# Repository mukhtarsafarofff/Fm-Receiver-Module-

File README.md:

(ENG)  Assembling an FM radio was always interesting for me , like another enthusiasts.  Outside of the TDA7000 IC there is only one tunable LC circuit for the local oscillator . So complete FM radio can be made enough small to be fit inside cigarette lighter.The audio output of the receiver is amplified through LM386 amplifier chip that can drive a small speaker or headphones. Thehe superheterodine receiver: the mixer, the oscillator, the IF amplifier, the amplitude limiter, the FM detector and few others.The station signal is from the (telescopiut circuit that consists of L2, C13, C12 and C14. It is a parallel oscillatory circuit damped with R3 resistor, which has the reception bandwidth from 88 MHz till 108 MHz (it admits all the UHF signals on the pin 13, and weakens te signals outside the reception bandwidth). Inside the IC the s
(DEU) Das Zusammenbauen eines UKW-Radios war für mich immer interessant, wie auch für andere Enthusiasten. Außerhalb des TDA7000 IC gibt es nur einen einstellbaren LC-Schwingkreis für den lokalen Oszillator. So kann ein komplettes UKW-Radio klein genug gebaut werden, um in ein Feuerzeug zu passen. Der Audioausgang des Empfängers wird durch den LM386 Verstärkerchip verstärkt, der einen kleinen Lautsprecher oder Kopfhörer antreiben kann. Das elektronische Diagramm des HF-Teils des Geräts (von der Antenne bis zum NF-Ausgang) mit dem TDA7000 ist auf Bild 4.7 dargestellt. Wie man sehen kann, ist es ein einfaches Gerät, das mit einer relativ kleinen Anzahl von Komponenten gebaut ist. Der IC enthält alle Stufen des Überlagerungsempfängers: den Mischer, den Oszillator, den ZF-Verstärker, den Amplitudenbegrenzer, den FM-Detektor und einige andere. Das Signals der Station wird von der (teleskopischen) Antenne zum Eingangskreis geführt, der aus L2, C13, C12 und C14 besteht. Es ist ein gedämpfter Parallelschwingkreis mit einem R3-Widerstand, der eine Empfangsbandbreite von 88 MHz bis 108 MHz hat (er lässt alle UHF-Signale am Pin 13 zu und schwächt die Signale außerhalb der Empfangsbandbreite ab). Innerhalb des IC werden die Signale in den Mischer geleitet, wo sie neue Trägerfrequenzen erhalten.  Der ZF-Verstärker folgt dann, der nur eines dieser Signale verstärkt, dessen Frequenz gleich der Zwischenfrequenz ist, gefolgt vom Begrenzer, dem FM-Detektor, dem Stummschaltkreis und dem NF-Vorverstärker.  Der Schwingkreis des lokalen Oszillators (L1, Cp, Cs, C und C5) ist zwischen den Pins 5 und 6 geschaltet.  Bild 4.8-a zeigt die Leiterplatte des Geräts von Bild 4.7, während Bild 4.8-b das Komponentenlayout (auf der Leiterplatte) enthält.  Das komplette Gerät ist auf Bild 4.8-c zu sehen.  Der variable Kondensator von Bild 3.8 wird hier als einziger variabler Kondensator verwendet, da der Eingangskreis aperiodisch ist, die Beine mit FO und G gekennzeichnet sind.  Dieser Kondensator dient dazu, den Empfänger auf Stationen einzustellen.  Im NF-Teil des Empfängers wird der Verstärker, der mit dem LM386 von Bild 3.19 gebaut ist, verwendet (die Teile links vom Potentiometer sind weggelassen). L1 und L2 sind die selbsttragenden Spulen.

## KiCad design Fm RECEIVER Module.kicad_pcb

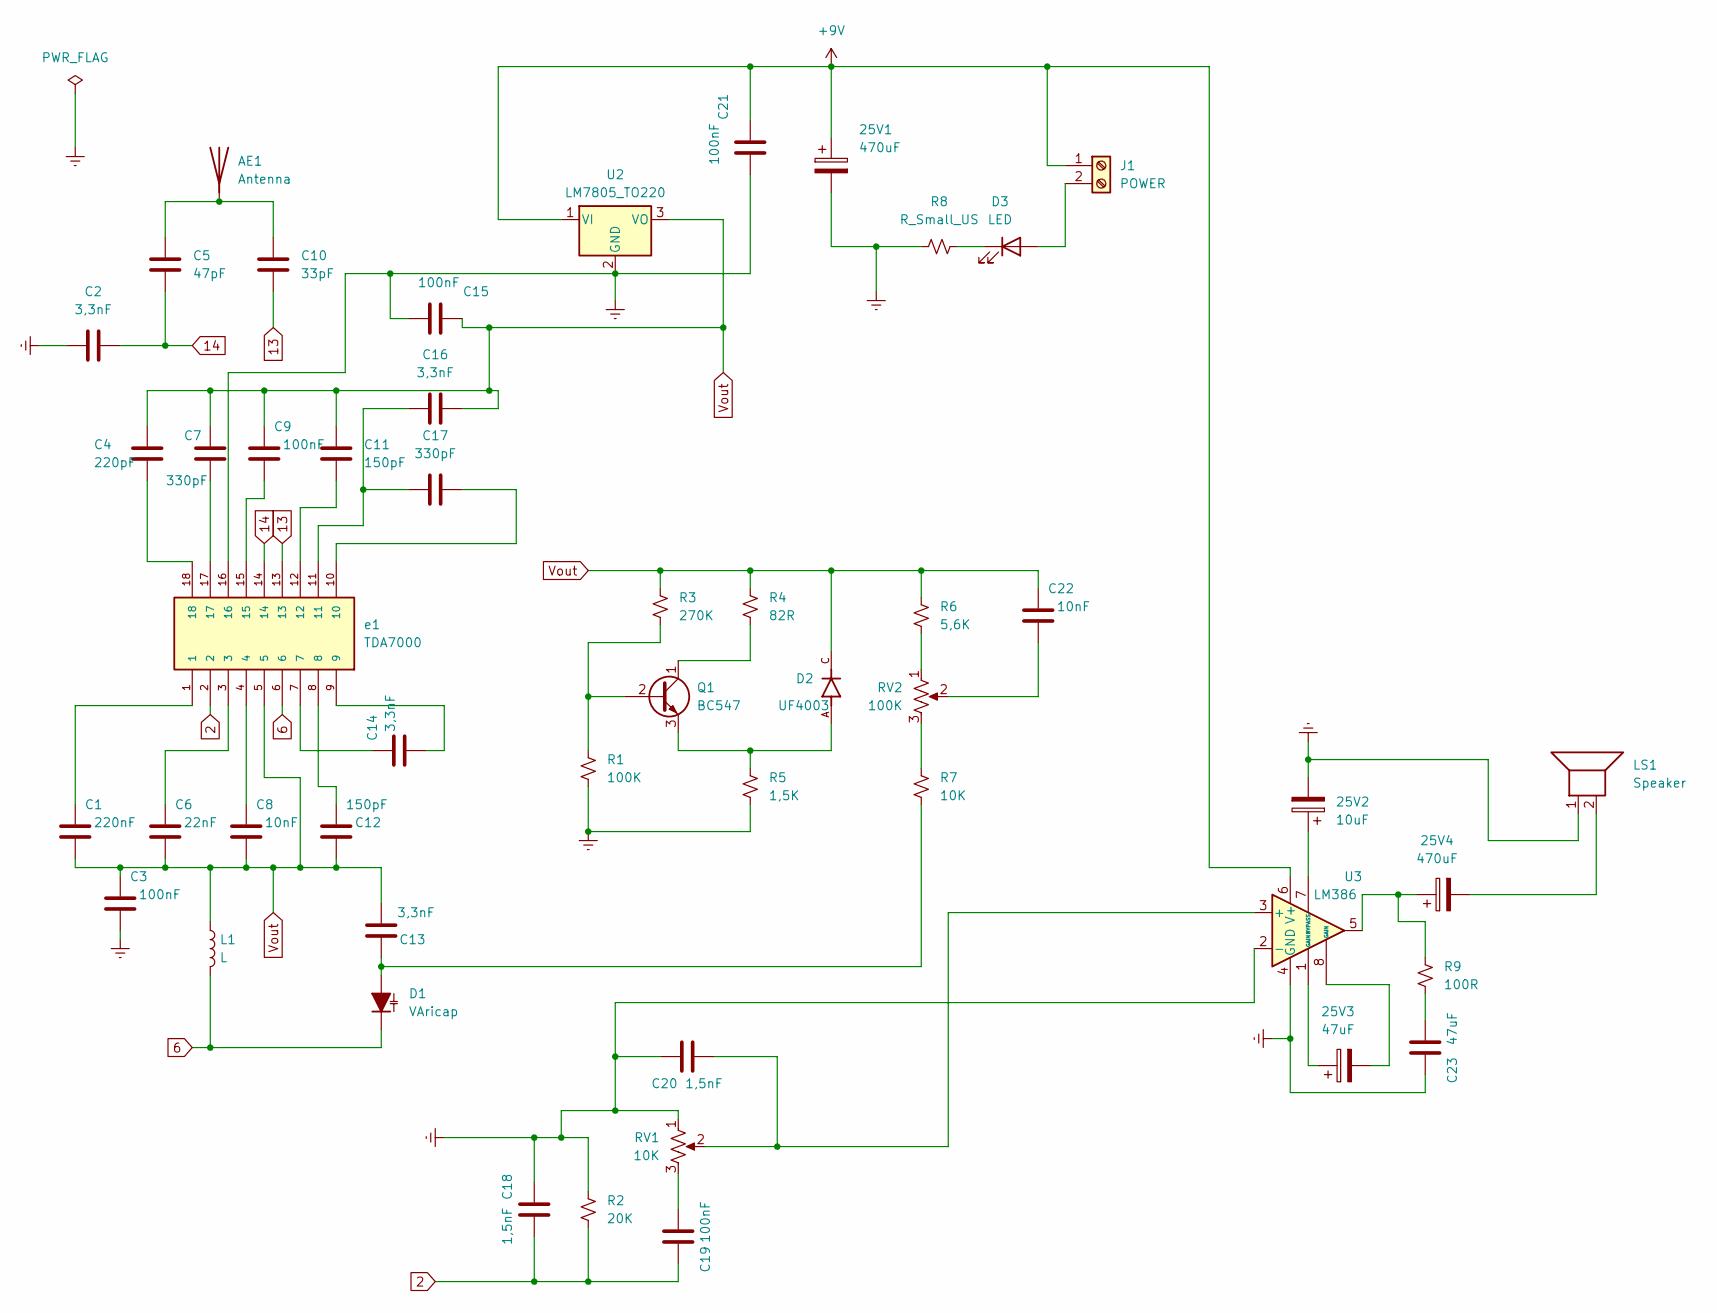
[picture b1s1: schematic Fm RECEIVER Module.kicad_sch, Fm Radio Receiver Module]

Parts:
25V1: 470uF; CP_Radial_D10.0mm_P7.50mm
25V2: 10uF; CP_Radial_D13.0mm_P7.50mm
25V3: 47uF; CP_Radial_D13.0mm_P7.50mm
25V4: 470uF; CP_Radial_D13.0mm_P7.50mm
AE1: Antenna; TerminalBlock_MetzConnect_360271_1x01_Horizontal_ScrewM3.0_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
C1: 220nF; C_Disc_D7.5mm_W5.0mm_P7.50mm
C2, C13, C14, C16: 3,3nF; C_Disc_D7.5mm_W5.0mm_P7.50mm
C3, C9, C15, C19, C21: 100nF; C_Disc_D7.5mm_W5.0mm_P7.50mm
C4: 220pF; C_Disc_D7.5mm_W5.0mm_P7.50mm
C5: 47pF; C_Disc_D7.5mm_W5.0mm_P7.50mm
C6: 22nF; C_Disc_D7.5mm_W5.0mm_P7.50mm
C7, C17: 330pF; C_Disc_D7.5mm_W5.0mm_P7.50mm
C8, C22: 10nF; C_Disc_D7.5mm_W5.0mm_P7.50mm
C10: 33pF; C_Disc_D7.5mm_W5.0mm_P7.50mm
C11, C12: 150pF; C_Disc_D7.5mm_W5.0mm_P7.50mm
C18, C20: 1,5nF; C_Disc_D7.5mm_W5.0mm_P7.50mm
C23: 47uF; C_Disc_D7.5mm_W5.0mm_P7.50mm
D1: VAricap; D_T-1_P12.70mm_Horizontal
D2: UF4003; DIOAD1055W87L533D272; PARTREV N/A
D3: LED; LED_D5.0mm
J1: POWER; TerminalBlock_bornier-2_P5.08mm
L1: L; L_Toroid_Horizontal_D12.7mm_P20.00mm_Diameter14-5mm_Amidon-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
LS1: Speaker; Indicator_PUI_AI-1440-TWT-24V-2-R
Q1: BC547; TO-92_Inline
R1: 100K; R_Axial_DIN0414_L11.9mm_D4.5mm_P15.24mm_Horizontal
R2: 20K; R_Axial_DIN0414_L11.9mm_D4.5mm_P15.24mm_Horizontal
R3: 270K; R_Axial_DIN0414_L11.9mm_D4.5mm_P15.24mm_Horizontal
R4: 82R; R_Axial_DIN0414_L11.9mm_D4.5mm_P15.24mm_Horizontal
R5: 1,5K; R_Axial_DIN0414_L11.9mm_D4.5mm_P15.24mm_Horizontal
R6: 5,6K; R_Axial_DIN0414_L11.9mm_D4.5mm_P15.24mm_Horizontal
R7: 10K; R_Axial_DIN0414_L11.9mm_D4.5mm_P15.24mm_Horizontal
R8: R_Small_US; R_Axial_DIN0414_L11.9mm_D4.5mm_P15.24mm_Horizontal
R9: 100R; R_Axial_DIN0414_L11.9mm_D4.5mm_P15.24mm_Horizontal
RV1: 10K; Potentiometer_Vishay_148-149_Single_Horizontal
RV2: 100K; Potentiometer_Vishay_148-149_Single_Horizontal
U2: LM7805_TO220; TO-220-3_Vertical
U3: LM386; DIP-8_W7.62mm
e1: TDA7000; DIP-18_W7.62mm; PARTREV MAY 1992

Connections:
2: C18.2, C19.1, R2.1, e1.2
6: D1.1 (K), L1.2, e1.6
13: C10.2, e1.13
14: C2.2, C5.2, e1.14
+9V: 25V1.1, C21.1, J1.1, U2.1 (VI), U3.6 (V+)
Earth: 25V1.2, 25V2.2, C2.1, C3.2, C15.2, C18.1, C20.1, C21.2, C23.1, LS1.1, R1.2, R2.2, R5.2, R8.1, RV1.1, U2.2 (GND), U3.2 (-), U3.4 (GND), e1.16
unnamed: 25V3.1, U3.1 (GAIN)
unnamed: 25V3.2, U3.8 (GAIN)
unnamed: 25V4.1, R9.1, U3.5
unnamed: 25V4.2, LS1.2
unnamed: AE1.1 (A), C5.1, C10.1
unnamed: C1.1, e1.1
unnamed: C4.2, e1.18
unnamed: C6.1, e1.3
unnamed: C7.2, e1.17
unnamed: C8.1, e1.4
unnamed: C9.2, e1.15
unnamed: C11.2, e1.12
unnamed: C12.1, e1.8
unnamed: C14.1, e1.7
unnamed: C14.2, e1.9
unnamed: C16.1, C17.1, e1.11
unnamed: C17.2, e1.10
unnamed: C19.2, RV1.3
unnamed: C22.2, RV2.2
unnamed: C23.2, R9.2
unnamed: C13.1, D1.2 (A), R7.2
unnamed: D3.2 (A), J1.2
unnamed: D3.1 (K), R8.2
unnamed: Q1.2 (B), R1.1, R3.2
unnamed: Q1.1 (C), R4.2
unnamed: D2.A, Q1.3 (E), R5.1
unnamed: R6.2, RV2.1
unnamed: R7.1, RV2.3
unnamed: C20.2, RV1.2, U3.3 (+)
unnamed: 25V2.1, U3.7 (BYPASS)
Vout: C1.2, C3.1, C4.1, C6.2, C7.1, C8.2, C9.1, C11.1, C12.2, C13.2, C15.1, C16.2, C22.1, D2.C, L1.1, R3.1, R4.1, R6.1, U2.3 (VO), e1.5

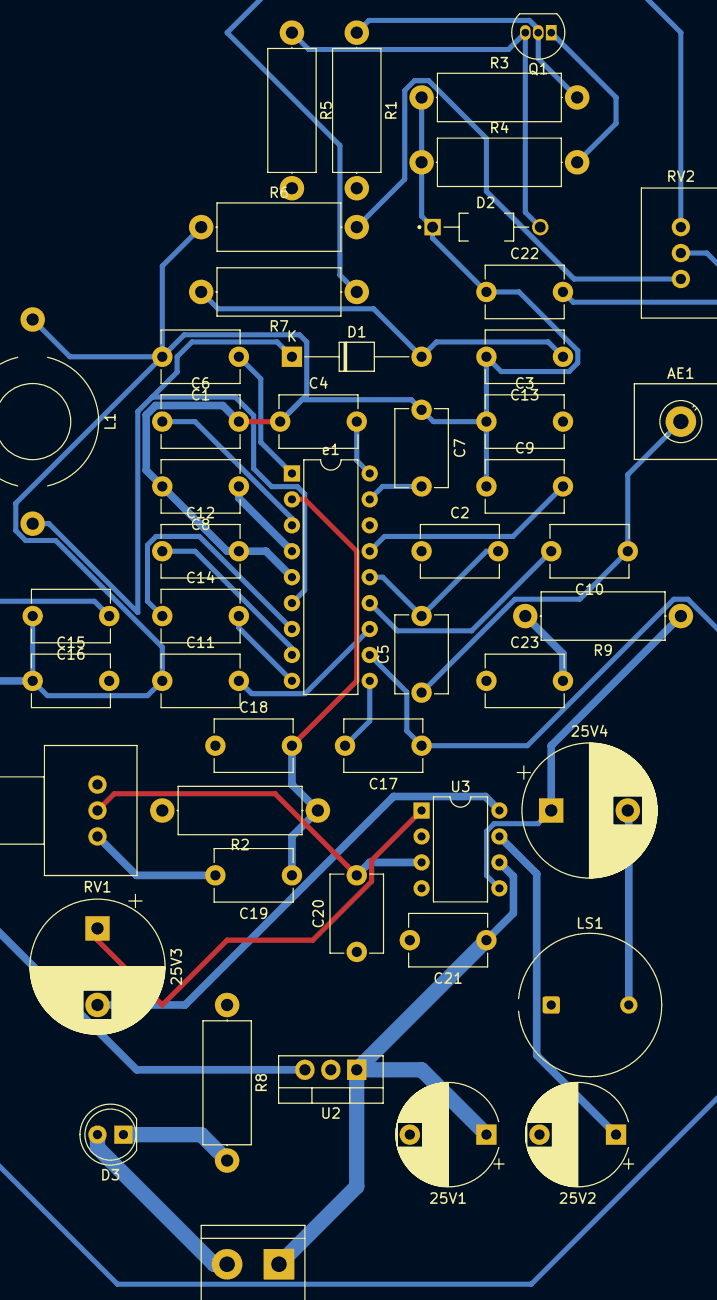
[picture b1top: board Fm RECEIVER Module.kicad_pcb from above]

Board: 2 copper layers, 49 parts (0 on the bottom side), 37 nets.

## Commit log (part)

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2024-03-25 Fm Receiver Module is accomplished
2024-08-01 Update README.md'
